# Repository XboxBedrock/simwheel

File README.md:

# Custom Simracing FFB Wheel

Hi! This is a custom-made Force Feedback Simracing steering wheel, made to somewhat resemble the 2019 Mercedes AMG F1 steering wheel, although not a direct replica. It is made using a hoverboard motor to save costs, and has a screen on the controller for the true F1 experience. For those who may not know what Force Feedback is, it's the usage of a motor to resist the motion of the player, to more closely mimic racecar steering, as the steering column in a racecar offers significant resistance to the driver. Generally this results in higher steering accuracy as humans are very good at gauging pressure accurately compared to distance, so resistance from a wheel helps with that. The wheel itself has a lot of buttons, as does every F1 steering wheel, to allow the driver to enable functions like pit lane steering limiter, etc. I am using keyswitches for a nice shifter experience, and a rotary encoder clutch pedal.

The premade setups you can get at this pricepoint do not offer the same selection of button and screen, and are lacking in torque (Often 2-3 Nm), so that made me want to make a much more capable wheel. There is significant complexity as the hub, wheel, and quickconnect all have to be designed. Overall I am a simracing fan and have always wanted to have a setup like this, but have been outpriced by the $700+ market rates, and figured this could be a great way to use my cad and pcb experience.

## Software

I intend to use a mix of the OpenFFBoard project's software (https://github.com/Ultrawipf/OpenFFBoard) and a small custom serial interface for the buttons and clutch pedal. As such this means you will plug in two USB cables to the computer, one for the wheel control and one for the buttons and clutch and display controller.

## Wiring Diagram

This is the full wiring diagram, the display unit will have 2 PCBs hooked up to it for the RPM status lights, and one to hold the shifter keyswitches (which is apart of buttons), as visible in the cad. All of the PCB design files can be found in the [kicad_project](./kicad_project/) folder. Here are the schematics and routing as images for sake of convinience however.

As to not spam this upper section with images, please check the [pcb images section](#pcb-images)

## CAD

All of the CAD was done in fusion 360, and while I *could* export my whole workspace, for the sake of sanity I uploaded the full assembly and just the wheel as two seperate files, the full assembly containing the wheel. Credit to GrabCAD for providing the models for some standard COTS parts (EG. ESP32, Power Supply, Magnetic Encoder Board, etc.).

## BOM

|Name                                                                |Price |Qty  |Expenditure|FIELD5|Link                                                                                                                                             |Notes:                                                |
|--------------------------------------------------------------------|------|-----|-----------|------|-------------------------------------------------------------------------------------------------------------------------------------------------|------------------------------------------------------|
|Hoverboard                                                          |$50   |1    |$50        |      |https://www.ebay.com/itm/316843156432                                                                                                            |                                                      |
|Ballbearings                                                        |$5.45 |1    |$5.45      |      |https://www.amazon.com/0-236-Precision-Chrome-Steel-Bearing/dp/B07L8MLK2N/                                                                       |                                                      |
|Springs                                                             |$5.30 |1    |$5.30      |      |https://www.amazon.com/uxcell-Compression-Spring-Stainless-Length/dp/B0C33CQ5LN/                                                                 |                                                      |
|Tactile Switch Buttons 12mm                                         |$0.06 |20   |$1.11      |      |https://lcsc.com/product-detail/Tactile-Switches_Megastar-ZX-QC1212-7-5CJ_C7470190.html?s_z=n_12mm%2520button                                    |                                                      |
|Rotary Encoder                                                      |$1.77 |12   |$21.24     |      |https://www.digikey.com/en/products/detail/bourns-inc/PEC11R-4225F-S0024/4499659                                                                 |Not in stock on LCSC, no similar models instock either|
|Neopixel Indiv                                                      |$4.95 |1    |$4.95      |      |https://www.adafruit.com/product/1938                                                                                                            |Only adafruit has in stock and/or sells :(            |
|WS2812B                                                             |$0.05 |30   |$1.47      |      |https://lcsc.com/product-detail/RGB-LEDs-Built-in-IC_XINGLIGHT-XL-5050RGBC-WS2812B_C2843785.html?s_z=n_ws2812b                                   |                                                      |
|470 Resistor                                                        |$0.00 |100  |$0.19      |      |https://lcsc.com/product-detail/Chip-Resistor-Surface-Mount_YAGEO-RC0805FR-0710KL_C84376.html?s_z=n_0805%2520470%2520ohm                         |                                                      |
|0.1uF Cap                                                           |$0.00 |100  |$0.46      |      |https://lcsc.com/product-detail/Multilayer-Ceramic-Capacitors-MLCC-SMD-SMT_YAGEO-CC0805KRX7R9BB104_C49678.html?s_z=n_capacitor%25200805%25200.1uF|                                                      |
|MX Blue                                                             |$1.25 |2    |$2.50      |      |https://www.digikey.com/en/products/detail/cherry-americas-llc/MX1A-E1NN/40084                                                                   |Not in stock on LCSC, no similar models instock either|
|M3 Screw Assortment                                                 |$9.99 |1    |$9.99      |      |https://www.amazon.com/Assortment-Stainless-Replacement-Machine-Fastener/dp/B0BMQFHDBH/                                                          |                                                      |
|M5 Screw + Nuts                                                     |$9.99 |1    |$9.99      |      |https://www.amazon.com/Assortment-Machine-Stainless-Washers-Threaded/dp/B0DFWW9DZK/                                                              |                                                      |
|4.3"LCD HDMI VGA,Video AV Driver Controller Board,TFT Module Display|$26.79|1    |$26.79     |      |https://www.buydisplay.com/4-3-lcd-hdmi-vga-video-av-driver-controller-board-tft-module-display                                                  |                                                      |
|Carbon Fibre Sticker Wrap                                           |$6.76 |1    |$6.76      |      |https://www.aliexpress.us/item/2251832843233677.html                                                                                             |                                                      |
|PCB                                                                 |$15   |1    |$15        |      |JLCPCB Cart                                                                                                                                      |                                                      |
|SK16 Linear Shaft Holders 4x                                        |$1.18 |1    |$1.18      |      |https://www.aliexpress.us/item/2255801037008492.html                                                                                             |                                                      |
|SK16 Linear Shaft Holders 2x                                        |$0.99 |1    |$0.99      |      |https://www.aliexpress.us/item/3256803971216207.html                                                                                             |                                                      |
|16mm Shaft                                                          |$7.59 |1    |$7.59      |      |https://www.amazon.com/uxcell-Linear-Hardened-Printer-Machine/dp/B0F32ZJCFC                                                                      |                                                      |
|MT6701 + Magnet                                                     |$0.99 |1    |$0.99      |      |https://www.aliexpress.us/item/3256808951558543.html                                                                                             |                                                      |
|OpenFFBoard                                                         |$34   |1    |$34        |      |https://www.elecrow.com/open-ffboard-stm32f407-usb-interface-only.html                                                                           |                                                      |
|96mm Fan                                                            |$8.67 |1    |$8.67      |      |https://www.digikey.com/en/products/detail/sunon-fans/MF92252V2-1000U-A99/7652235                                                                |Much to my awe, digikey has it for the cheapest?      |
|ODesc 4.2                                                           |$28.99|1    |$28.99     |      |https://flipsky.net/products/odesc-v4-2-24v-56v-controller                                                                                       |                                                      |
|600W PSU                                                            |$29.99|1    |$29.99     |      |https://www.amazon.com/BOSYTRO-Switching-Universal-Regulated-Security/dp/B0C53SLDM9/                                                             |                                                      |
|C14 Connector                                                       |$5.11 |1    |$5.11      |      |https://www.digikey.com/en/products/detail/te-connectivity-corcom-filters/1-6609987-4/1306112                                                    |                                                      |
|USBC Extension                                                      |$2    |1    |$2         |      |https://www.walmart.com/ip/onn-USB-C-Extension-Cable-White-6/153042914                                                                           |                                                      |
|XT90                                                                |11.99 |1    |11.99      |      |https://www.amazon.com/Female-Connector-Silicon-RC-Battery/dp/B08L3RS5HP/                                                                        |                                                      |
|12V Step-Down                                                       |8.99  |1    |8.99       |      |https://www.amazon.com/VOLRANTISE-Converter-Voltage-Regulator-Transformer/dp/B09WZ5WH8H?th=1                                                     |                                                      |
|VGA Connector                                                       |9.99  |1    |9.99       |      |https://www.amazon.com/uxcell-Connector-Terminal-Mechanical-Equipment/dp/B07LCM71MY/                                                             |                                                      |
|VGA Cable                                                           |5.28  |1    |5.28       |      |https://www.amazon.com/Pasow-Monitor-Cable-Computer-Projector/dp/B08B64KM93/                                                                     |                                                      |
|ESP32*3                                                               |12.99 |1    |12.99      |      |https://www.amazon.com/Development-ESP-WROOM-32-Bluetooth-Microcontroller-Compatible/dp/B0DSZTZKLM/                                              |                                                      |
|                                                                    |      |Total|**$330**       |      |Willing to incur any extra expense to myself                                                                                                     |                                                      |

## PCB Images

**Top Lights PCB**

**Safety Lights PCB**

**Shifter PCB**

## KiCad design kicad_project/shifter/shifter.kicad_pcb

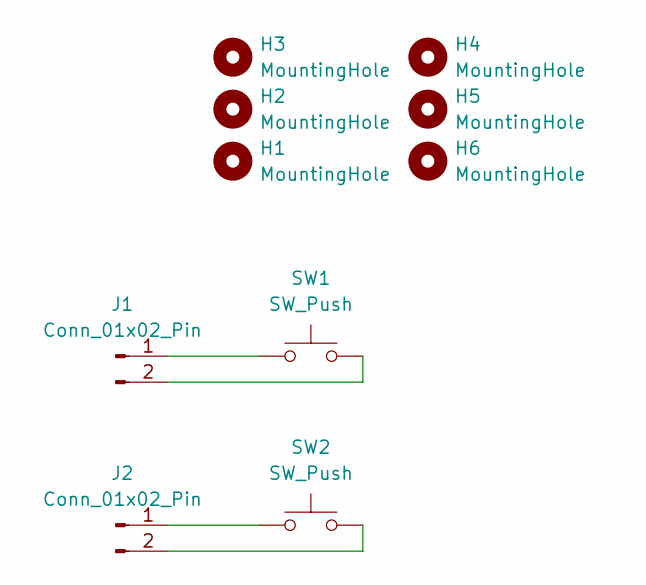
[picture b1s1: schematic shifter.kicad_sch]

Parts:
H1, H2, H3, H4, H5, H6: MountingHole; MountingHole_3.2mm_M3
J1, J2: Conn_01x02_Pin; PinHeader_1x02_P2.54mm_Vertical
SW1, SW2: SW_Push; SW_Cherry_MX_1.00u_PCB

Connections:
unnamed: J1.1, SW1.1
unnamed: J1.2, SW1.2
unnamed: J2.1, SW2.1
unnamed: J2.2, SW2.2

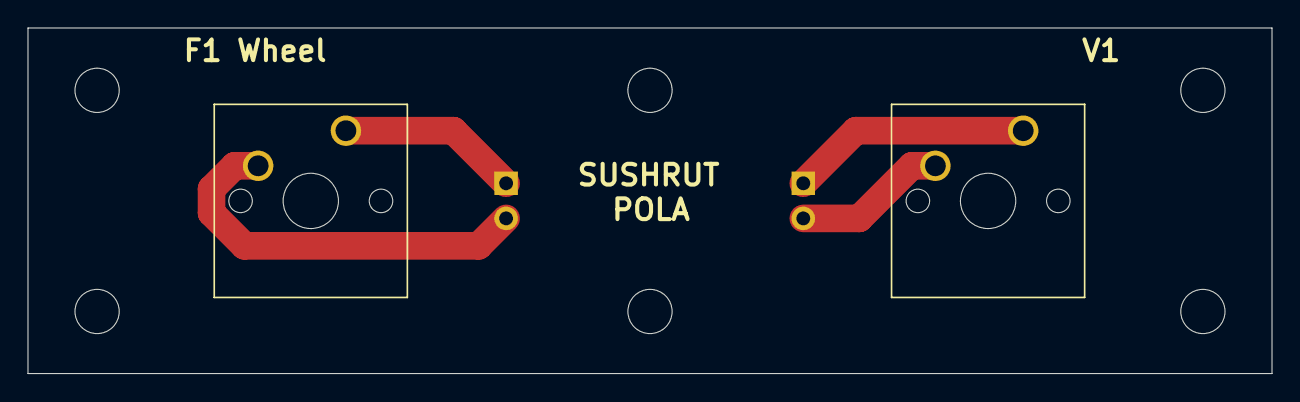
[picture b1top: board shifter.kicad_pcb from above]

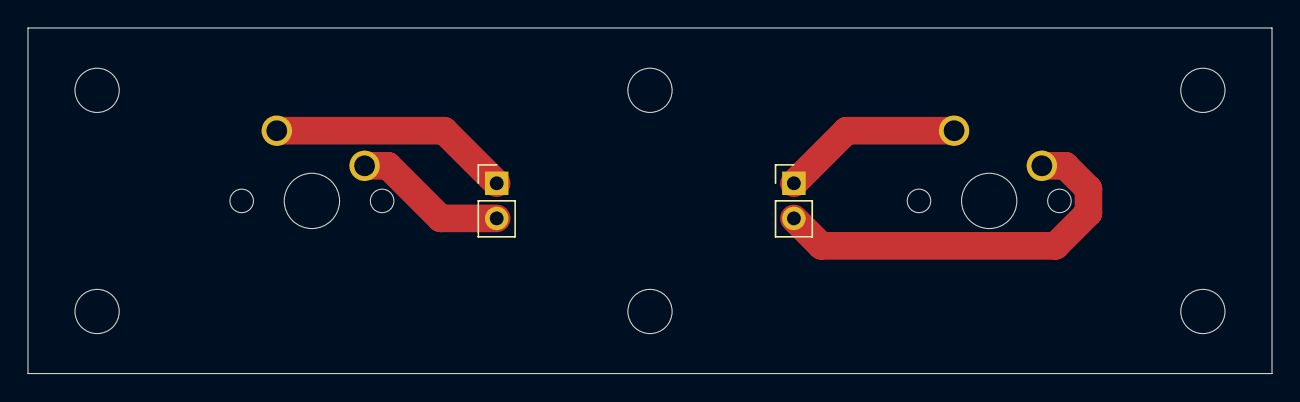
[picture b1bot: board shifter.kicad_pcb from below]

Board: 2 copper layers, 90.0 x 25.0 mm, 10 parts (2 on the bottom side), 4 nets.

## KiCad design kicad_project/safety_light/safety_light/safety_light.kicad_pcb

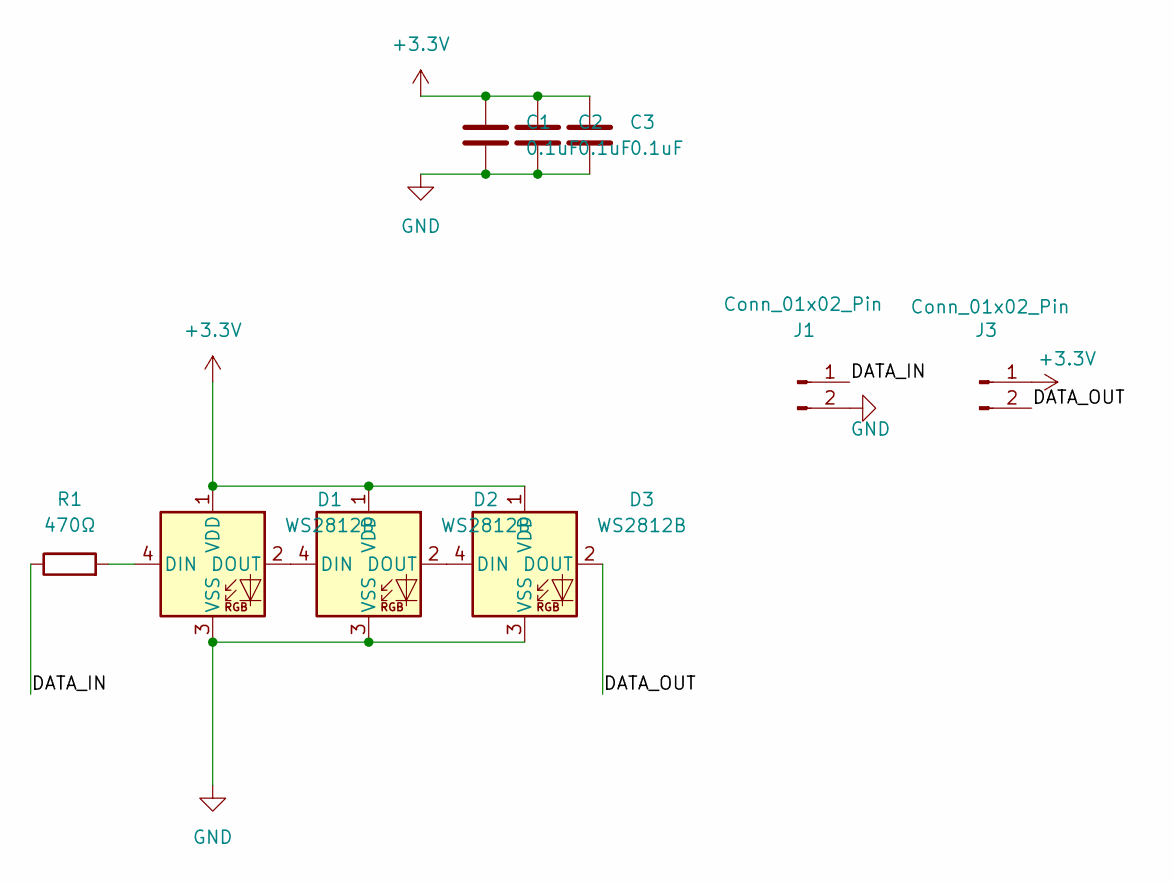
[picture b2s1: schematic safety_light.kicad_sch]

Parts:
C1, C2, C3: 0.1uF; C_0805_2012Metric
D1, D2, D3: WS2812B; LED_WS2812B_PLCC4_5.0x5.0mm_P3.2mm
J1, J3: Conn_01x02_Pin; PinHeader_1x02_P2.54mm_Vertical
R1: 470Ω; R_0805_2012Metric_Pad1.20x1.40mm_HandSolder

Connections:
+3.3V: C1.1, C2.1, C3.1, D1.1 (VDD), D2.1 (VDD), D3.1 (VDD), J3.1
/DATA_IN: J1.1, R1.1
/DATA_OUT: D3.2 (DOUT), J3.2
GND: C1.2, C2.2, C3.2, D1.3 (VSS), D2.3 (VSS), D3.3 (VSS), J1.2
unnamed: D1.4 (DIN), R1.2
unnamed: D1.2 (DOUT), D2.4 (DIN)
unnamed: D2.2 (DOUT), D3.4 (DIN)

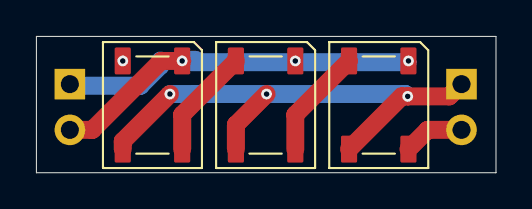
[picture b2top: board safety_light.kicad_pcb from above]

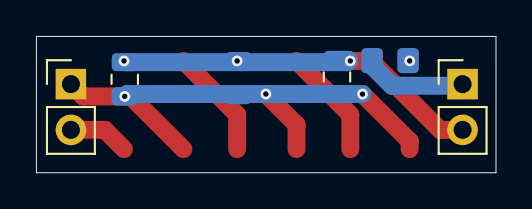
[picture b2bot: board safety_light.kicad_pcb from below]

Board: 2 copper layers, 25.5 x 7.6 mm, 9 parts (6 on the bottom side), 7 nets.

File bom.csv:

Name,Price,Qty,Expenditure,,Link,Notes:
Hoverboard,$50,1,$50,,https://www.ebay.com/itm/316843156432,
Ballbearings,$5.45,1,$5.45,,https://www.amazon.com/0-236-Precision-Chrome-Steel-Bearing/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,
Springs,$5.30,1,$5.30,,https://www.amazon.com/uxcell-Compression-Spring-Stainless-L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,
Tactile Switch Buttons 12mm,$0.06,20,$1.11,,https://lcsc.com/product-detail/Tactile-Switches_Megastar-ZX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,
Rotary Encoder,$1.77,12,$21.24,,https://www.digikey.com/en/products/detail/bourns-inc/PEC11R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,"Not in stock on LCSC, no similar models instock either"
Neopixel Indiv,$4.95,1,$4.95,,https://www.adafruit.com/product/1938,Only adafruit has in stock and/or sells :(
WS2812B,$0.05,30,$1.47,,https://lcsc.com/product-detail/RGB-LEDs-Built-in-IC_XINGLIG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,
470 Resistor,$0.00,100,$0.19,,https://lcsc.com/product-detail/Chip-Resistor-Surface-Mount_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,
0.1uF Cap,$0.00,100,$0.46,,https://lcsc.com/product-detail/Multilayer-Ceramic-Capacitor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,
MX Blue,$1.25,2,$2.50,,https://www.digikey.com/en/products/detail/cherry-americas-l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,"Not in stock on LCSC, no similar models instock either"
M3 Screw Assortment,$9.99,1,$9.99,,https://www.amazon.com/Assortment-Stainless-Replacement-Mach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,
M5 Screw + Nuts,$9.99,1,$9.99,,https://www.amazon.com/Assortment-Machine-Stainless-Washers-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,
"4.3""LCD HDMI VGA,Video AV Driver Controller Board,TFT Module Display",$26.79,1,$26.79,,https://www.buydisplay.com/4-3-lcd-hdmi-vga-video-av-driver-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,
Carbon Fibre Sticker Wrap,$6.76,1,$6.76,,https://www.aliexpress.us/item/2251832843233677.html,
PCB,$15,1,$15,,JLCPCB Cart,
SK16 Linear Shaft Holders 4x,$1.18,1,$1.18,,https://www.aliexpress.us/item/2255801037008492.html,
SK16 Linear Shaft Holders 2x,$0.99,1,$0.99,,https://www.aliexpress.us/item/3256803971216207.html,
16mm Shaft,$7.59,1,$7.59,,https://www.amazon.com/uxcell-Linear-Hardened-Printer-Machin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,
MT6701 + Magnet,$0.99,1,$0.99,,https://www.aliexpress.us/item/3256808951558543.html,
OpenFFBoard,$34,1,$34,,https://www.elecrow.com/open-ffboard-stm32f407-usb-interface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,
96mm Fan,$8.67,1,$8.67,,https://www.digikey.com/en/products/detail/sunon-fans/MF9225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,"Much to my awe, digikey has it for the cheapest?"
ODesc 4.2,$28.99,1,$28.99,,https://flipsky.net/products/odesc-v4-2-24v-56v-controller,
600W PSU,$29.99,1,$29.99,,https://www.amazon.com/BOSYTRO-Switching-Universal-Regulated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,
C14 Connector,$5.11,1,$5.11,,https://www.digikey.com/en/products/detail/te-connectivity-c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,
USBC Extension,$2,1,$2,,https://www.walmart.com/ip/onn-USB-C-Extension-Cable-White-6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,
XT90,11.99,1,11.99,,https://www.amazon.com/Female-Connector-Silicon-RC-Battery/d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,
12V Step-Down,8.99,1,8.99,,https://www.amazon.com/VOLRANTISE-Converter-Voltage-Regulato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,
VGA Connector,9.99,1,9.99,,https://www.amazon.com/uxcell-Connector-Terminal-Mechanical-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,
VGA Cable,5.28,1,5.28,,https://www.amazon.com/Pasow-Monitor-Cable-Computer-Projecto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,
ESP32,12.99,1,12.99,,https://www.amazon.com/Development-ESP-WROOM-32-Bluetooth-Mi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,
,,,,,,
,,,,,,
,,,,,,
,,,,,,
,,,,,,
,,,,,,
,,,,,,
,,Total,$330,,Willing to incur any extra expense to myself,

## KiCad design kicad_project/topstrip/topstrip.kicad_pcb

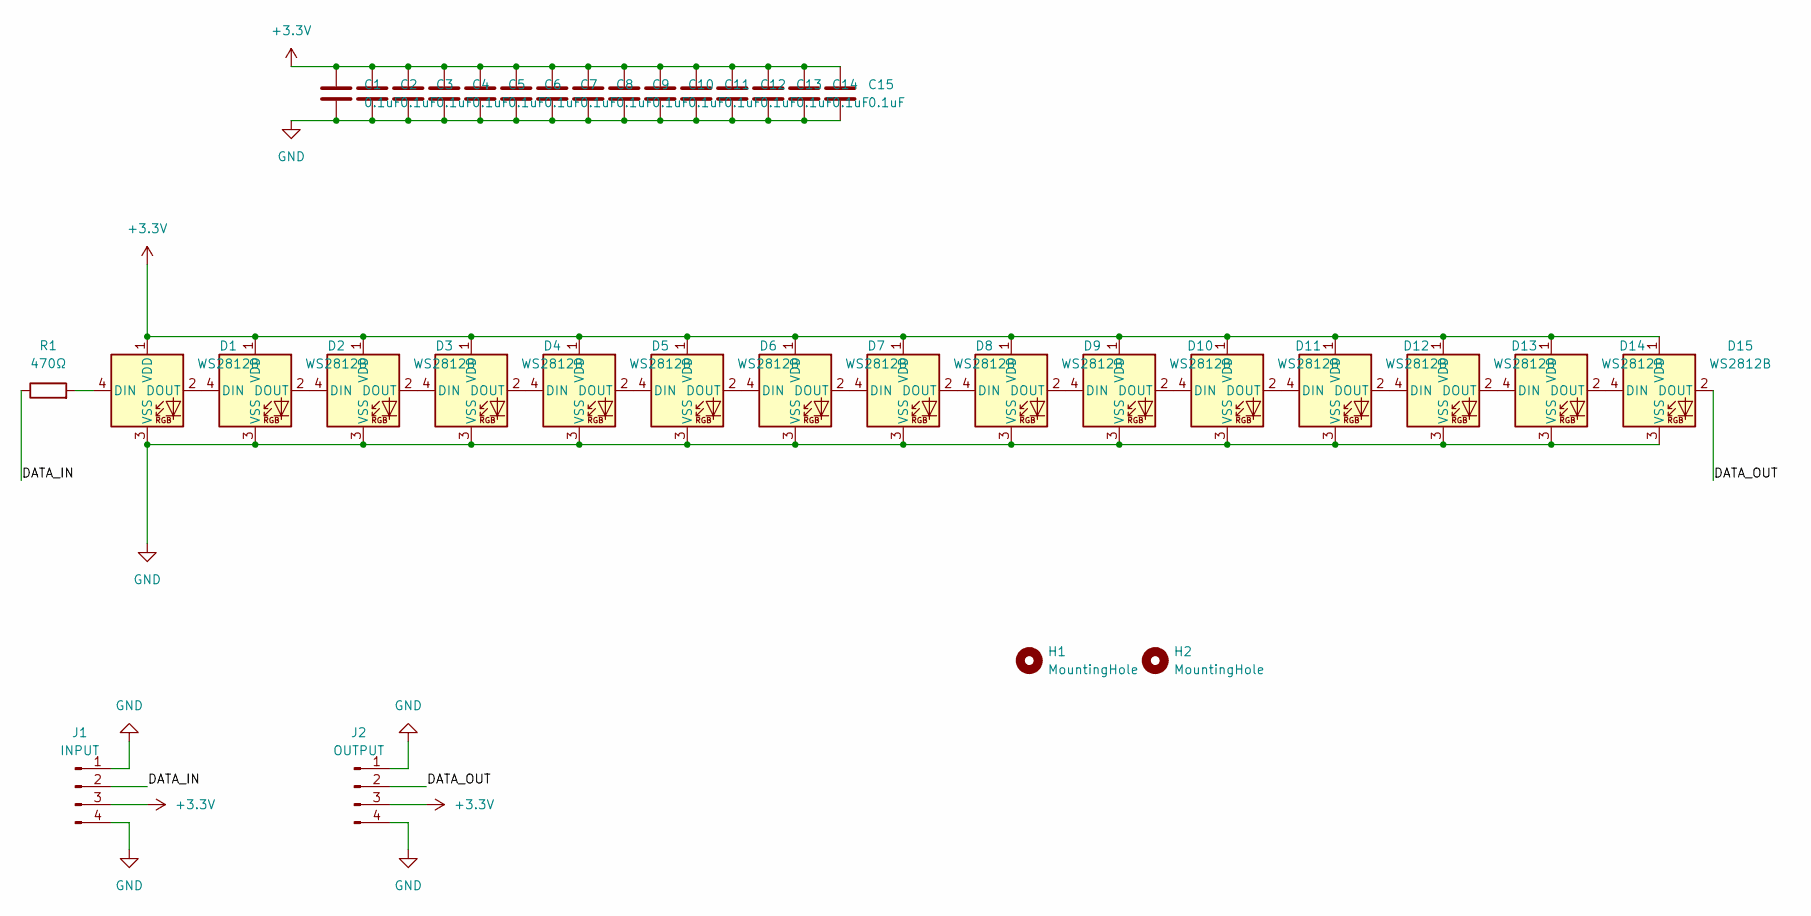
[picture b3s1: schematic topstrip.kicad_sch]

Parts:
C1, C2, C3, C4, C5, C6, C7, C8, C9, C10, C11, C12, C13, C14, C15: 0.1uF; C_0805_2012Metric
D1, D2, D3, D4, D5, D6, D7, D8, D9, D10, D11, D12, D13, D14, D15: WS2812B; LED_WS2812B_PLCC4_5.0x5.0mm_P3.2mm
H1, H2: MountingHole; MountingHole_3.2mm_M3_DIN965
J1: INPUT; PinHeader_1x04_P2.54mm_Vertical
J2: OUTPUT; PinHeader_1x04_P2.54mm_Vertical
R1: 470Ω; R_0805_2012Metric_Pad1.20x1.40mm_HandSolder

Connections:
+3.3V: C1.1, C2.1, C3.1, C4.1, C5.1, C6.1, C7.1, C8.1, C9.1, C10.1, C11.1, C12.1, C13.1, C14.1, C15.1, D1.1 (VDD), D2.1 (VDD), D3.1 (VDD), D4.1 (VDD), D5.1 (VDD), D6.1 (VDD), D7.1 (VDD), D8.1 (VDD), D9.1 (VDD), D10.1 (VDD), D11.1 (VDD), D12.1 (VDD), D13.1 (VDD), D14.1 (VDD), D15.1 (VDD), J1.3, J2.3
/DATA_IN: J1.2, R1.1
/DATA_OUT: D15.2 (DOUT), J2.2
GND: C1.2, C2.2, C3.2, C4.2, C5.2, C6.2, C7.2, C8.2, C9.2, C10.2, C11.2, C12.2, C13.2, C14.2, C15.2, D1.3 (VSS), D2.3 (VSS), D3.3 (VSS), D4.3 (VSS), D5.3 (VSS), D6.3 (VSS), D7.3 (VSS), D8.3 (VSS), D9.3 (VSS), D10.3 (VSS), D11.3 (VSS), D12.3 (VSS), D13.3 (VSS), D14.3 (VSS), D15.3 (VSS), J1.1, J1.4, J2.1, J2.4
unnamed: D1.4 (DIN), R1.2
unnamed: D1.2 (DOUT), D2.4 (DIN)
unnamed: D2.2 (DOUT), D3.4 (DIN)
unnamed: D3.2 (DOUT), D4.4 (DIN)
unnamed: D4.2 (DOUT), D5.4 (DIN)
unnamed: D5.2 (DOUT), D6.4 (DIN)
unnamed: D6.2 (DOUT), D7.4 (DIN)
unnamed: D7.2 (DOUT), D8.4 (DIN)
unnamed: D8.2 (DOUT), D9.4 (DIN)
unnamed: D9.2 (DOUT), D10.4 (DIN)
unnamed: D10.2 (DOUT), D11.4 (DIN)
unnamed: D11.2 (DOUT), D12.4 (DIN)
unnamed: D12.2 (DOUT), D13.4 (DIN)
unnamed: D13.2 (DOUT), D14.4 (DIN)
unnamed: D14.2 (DOUT), D15.4 (DIN)

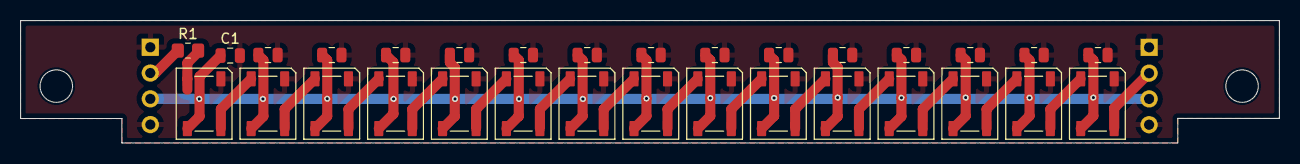
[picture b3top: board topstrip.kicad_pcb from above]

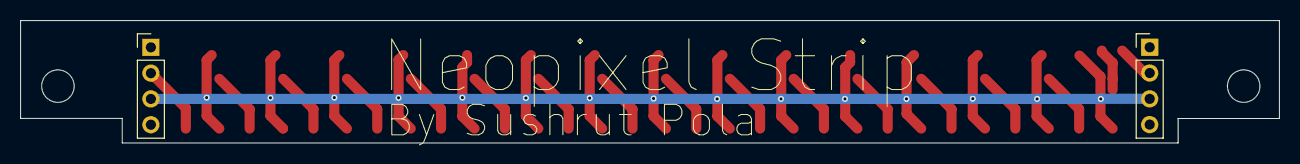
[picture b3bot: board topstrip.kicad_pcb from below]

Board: 2 copper layers, 124.0 x 12.1 mm, 35 parts (2 on the bottom side), 19 nets.

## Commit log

2025-07-16 project
2025-07-16 make readme look nicer
